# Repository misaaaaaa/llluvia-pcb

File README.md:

# llluvia-pcb

Circuito generador de gotas de lluvia lumínicas y sonoras

Fotografía por Carolina Miguieles en la inauguración de la muestra

## Descripción

El circuito utiliza un transistor NPN de manera que genera un ruido rosa. Con la base conectada a negativo, el emisor a positivo y el colector desconectado, se genera una conducción inversa a través de la unión base-emisor. Esta configuración crea fluctuaciones aleatorias de corriente que producen variaciones similares al ruido rosa, lo que asemeja el sonido de una lluvia torrencial. Esta señal es llevada a un comparador simple, al que por medio de un potenciómetro se puede controlar cuantas "gotas" se dejan pasar.

## Especificaciones

- Alimentación sugerida de 12 a 15v DC centro positivo
- Alimentación vía batería 23A o fuente de poder DC
- Potenciómetro de control de "gotas"
- Potenciómetro de control de nivel
- Salida para auriculares o de línea (revisar bugs)

## Contexto

La pcb fue diseñada para la exposición "Llluvia Metropolitana", exhibida en enero de 2026 en la Galería Metropolitana junto a Rainer Krause. Se produjeron tres modelos, todos con la misma electrónica, pero con una cita, traducción o paráfrasis distinta en cada una:

"[...] ya va a llover, ya va a llover, ya va a llover, ya va a llover, [...]" - Steve Reich

"pensar en el evento pluvial del carniense: 
la lluvia de 2 millones de años hace 234 millones de años (*archifósil*)" - Quentin Meillassoux

"¿la lluvia pertenece al mundo material, o solo los charcos que deja en zanjas y baches?" - Tim Ingold

## Bugs conocidos

- Para trabajar conectado a una fuente DC se sugiere retirar la batería de 12V 23A, ya que según el circuito solo se desconecta si ambas entradas JACK DC tienen algo conectado
- La salida L y R del conector de audio están puenteadas, por lo que si se conecta un plug MONO (TS) como los del formato Eurorack la salida se aterriza y no suena. Se sugiere intervenir la placa y romper la pista que conecta ambas salidas si se va a utilizar de esta manera. Si se usa con audífonos o con un cable TRS no hay inconvenientes.

## Bom

[Lista de materiales en formato CSV](./llluvia-bom.csv)

| Reference       | Cantidad | Value                     | Footprint                                              | Comentario                                        | Link de referencia                                                                        |
|-----------------|----------|---------------------------|--------------------------------------------------------|---------------------------------------------------|-------------------------------------------------------------------------------------------|
| C1,C2           |        2 | 1u                        | Condensador no polarizado 5.1mm x 3.2mm - Pitch 5.00mm |                                                   | ~                                                                                         |
| D1,D3,D4        |        3 | LED                       | Led 3mm cabeza plana                                   | Montaje invertido (por parte trasera de la placa) | <https://www.railwayscenics.com/flat-warm-white-water-clear-resistor-reqd-p-4583.html>      |
| D2              |        1 | 1N4007                    | Diodo THT TO-41                                        |                                                   | <http://www.vishay.com/docs/88503/1n4001.pdf>                                               |
| J2,J3           |        2 | JACK_DC                   | Conector Barrel Jack 2.1mm x 5.5 mm                    |                                                   | <https://es.rs-online.com/web/p/conectores-de-alimentacion-dc/2858785>                      |
| J4              |        1 | ON/OFF                    | Pin header 2p 2.54mm                                   |                                                   | <https://no.rs-online.com/web/p/pcb-headers/2518086>                                        |
| J5              |        1 | AudioJack2_Ground_Switch  | Jack audio TRS 3.5mm modelo CUI SJ1-3525N              |                                                   | <https://forum.digikey.com/t/cui-sj1-3525n-series-3-5mm-audio-jack-suffix-information/6667> |
| Q2              |        1 | 2N2222A                   | Transistor 2n2222a THT                                 |                                                   | <https://www.victronics.cl/transistores/transistor-pn2222a-npn-06a-40v-to92-10u/>                                        |
| R1              |        1 | 1M                        | Resistencia 1/4w                                       |                                                   | ~                                                                                         |
| R2              |        1 | 470k                      | Resistencia 1/4w                                       |                                                   | ~                                                                                         |
| R3              |        1 |                       220 | Resistencia 1/4w                                       |                                                   | ~                                                                                         |
| R4,R6,R7,R8,R11 |        5 | 1k                        | Resistencia SMD 0805                                   | Para practicar soldadura SMD a mano :D            | ~                                                                                         |
| R5,R9,R10       |        3 | 100k                      | Resistencia SMD 0805                                   | Para practicar soldadura SMD a mano :D            | ~                                                                                         |
| RV1,RV2         |        2 | 100k                      | Potenciómetro PCB tipo RV09 o PTV09A Vertical          |                                                   | <https://es.rs-online.com/web/p/potenciometros/7377827>                                     |
| U1              |        1 | LM324                     | Circuito Integrado DIP-14 + Socket                     |                                                   | <http://www.ti.com/lit/ds/symlink/lm2902-n.pdf>                                             |
| BT1             |        1 | Batería 12V A23 + Soporte | 12v A23 battery holder THT                             | Solo si se quiere usar con batería                | <https://www.jsumo.com/battery-holder-1-x-23a-with-pins>                                    |

## Esquemático

## Imágenes

## Video de referencia (01:40)

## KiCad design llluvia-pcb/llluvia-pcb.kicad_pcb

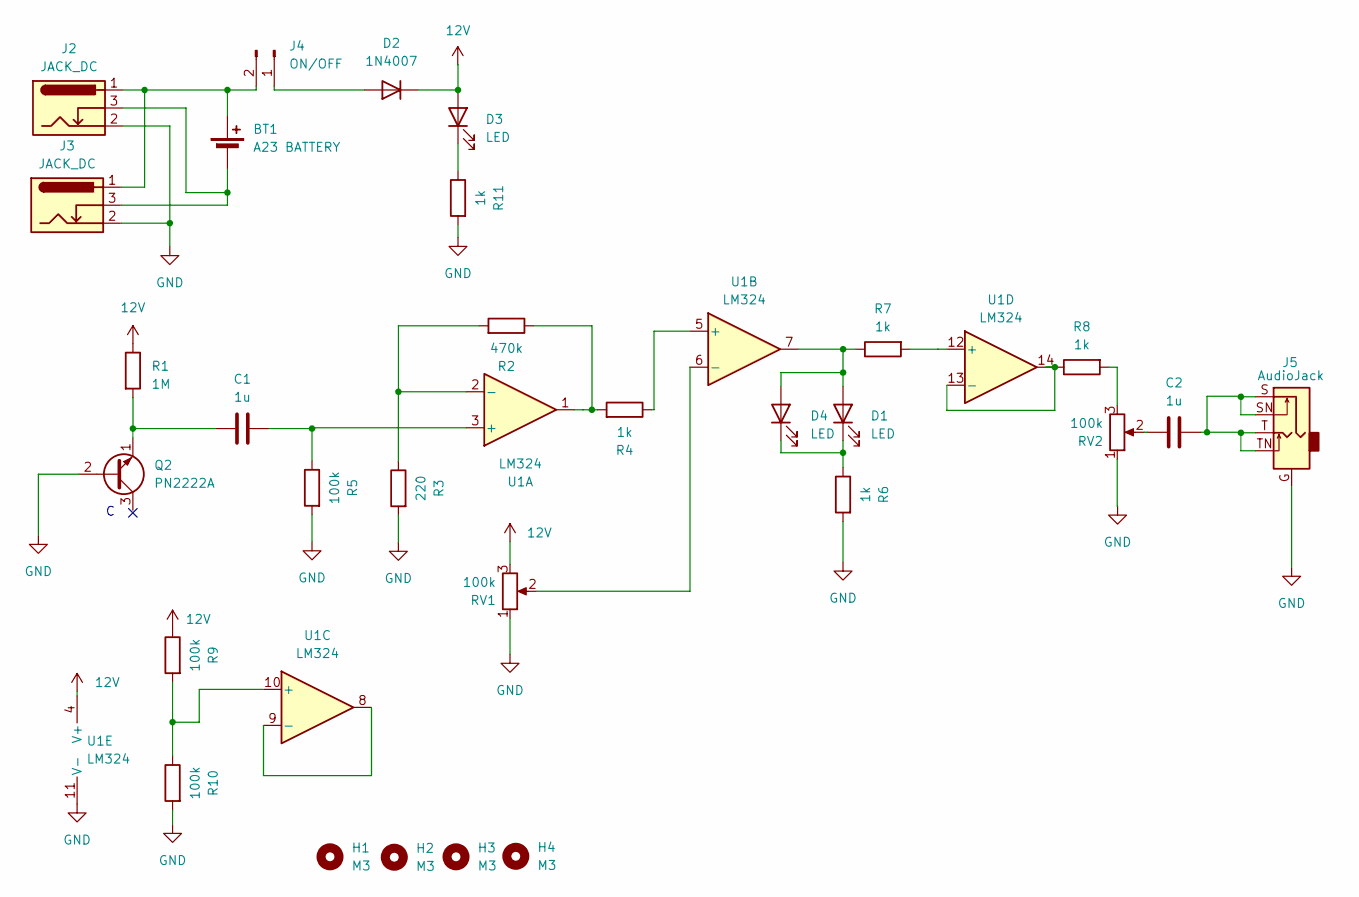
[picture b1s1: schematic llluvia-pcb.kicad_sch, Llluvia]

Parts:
BT1: A23 BATTERY; Battery_23A
C1, C2: 1u; C_Disc_D5.1mm_W3.2mm_P5.00mm
D1, D3: LED; LED_PCBasDiffuser
D2: 1N4007; D_DO-41_SOD81_P10.16mm_Horizontal
D4: LED; LED_D5.0mm
H1, H2, H3, H4: M3; MountingHole_3.2mm_M3
J2, J3: JACK_DC; BarrelJack_Horizontal
J4: ON/OFF; PinHeader_1x02_P2.54mm_Vertical
J5: AudioJack; Jack_3.5mm_CUI_SJ1-3525N_Horizontal
Q2: PN2222A; TO-92_Inline_Wide
R1: 1M; R_Axial_DIN0207_L6.3mm_D2.5mm_P10.16mm_Horizontal
R2: 470k; R_Axial_DIN0207_L6.3mm_D2.5mm_P10.16mm_Horizontal
R3: 220; R_Axial_DIN0207_L6.3mm_D2.5mm_P10.16mm_Horizontal
R4, R6, R7, R8, R11: 1k; R_0805_2012Metric_Pad1.20x1.40mm_HandSolder
R5, R9, R10: 100k; R_0805_2012Metric_Pad1.20x1.40mm_HandSolder
RV1, RV2: 100k; Potentiometer_Bourns_PTV09A-1_Single_Vertical
U1: LM324; DIP-14_W7.62mm_LongPads

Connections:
12V: D2.1 (K), D3.2 (A), R1.1, R9.1, RV1.3, U1.4 (V+)
GND: J2.2, J3.2, J5.G, Q2.2 (B), R3.2, R5.2, R6.2, R10.2, R11.2, RV1.1, RV2.1, U1.11 (V-)
unnamed: BT1.1 (+), J2.1, J3.1, J4.2
unnamed: BT1.2 (-), J2.3, J3.3
unnamed: C2.1, RV2.2
unnamed: C2.2, J5.S, J5.SN, J5.T, J5.TN
unnamed: D1.2 (A), D4.2 (A), R7.1, U1.7
unnamed: D1.1 (K), D4.1 (K), R6.1
unnamed: D2.2 (A), J4.1
unnamed: D3.1 (K), R11.1
unnamed: C1.1, Q2.1 (E), R1.2
unnamed: R2.1, R4.2, U1.1
unnamed: R8.2, RV2.3
unnamed: C1.2, R5.1, U1.3 (+)
unnamed: R2.2, R3.1, U1.2 (-)
unnamed: R4.1, U1.5 (+)
unnamed: RV1.2, U1.6 (-)
unnamed: R9.2, R10.1, U1.10 (+)
unnamed: U1.8, U1.9 (-)
unnamed: R7.2, U1.12 (+)
unnamed: R8.1, U1.13 (-), U1.14

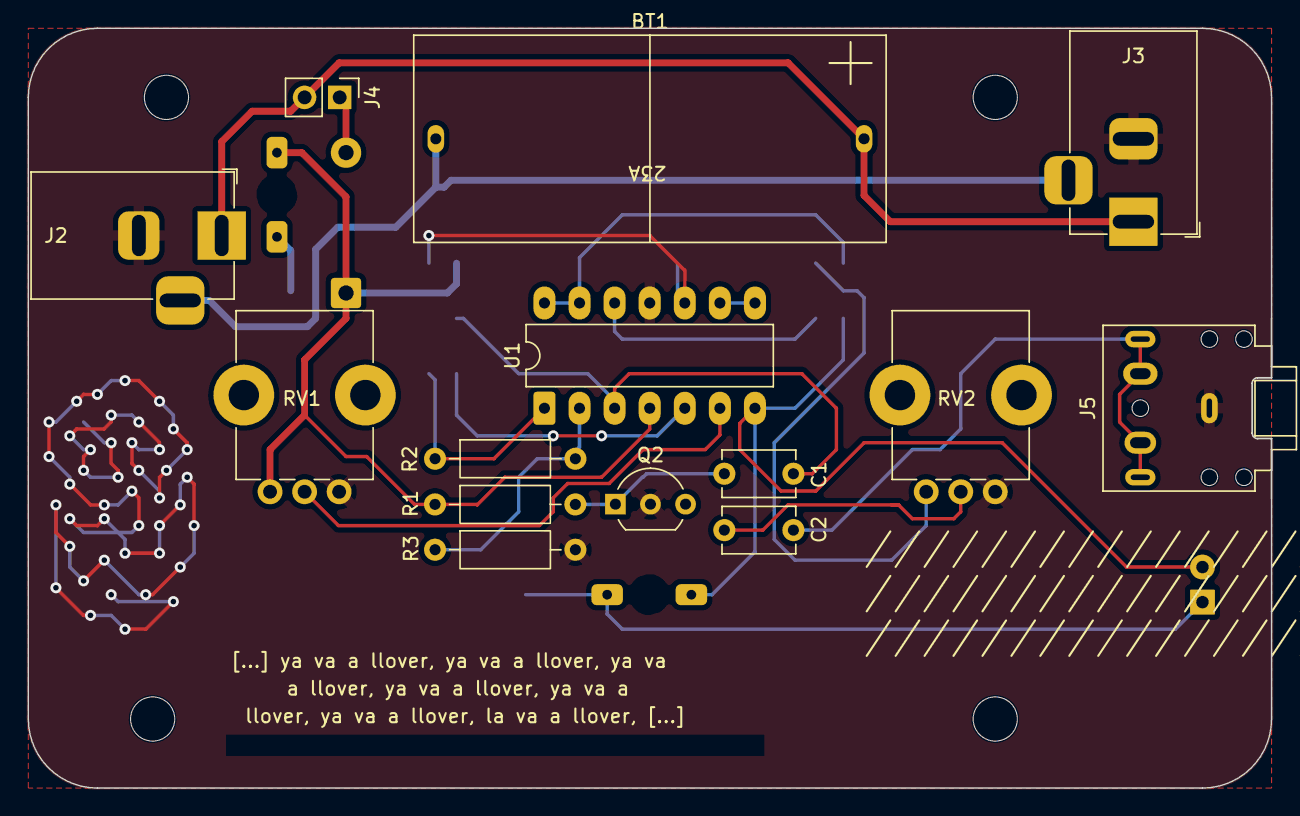
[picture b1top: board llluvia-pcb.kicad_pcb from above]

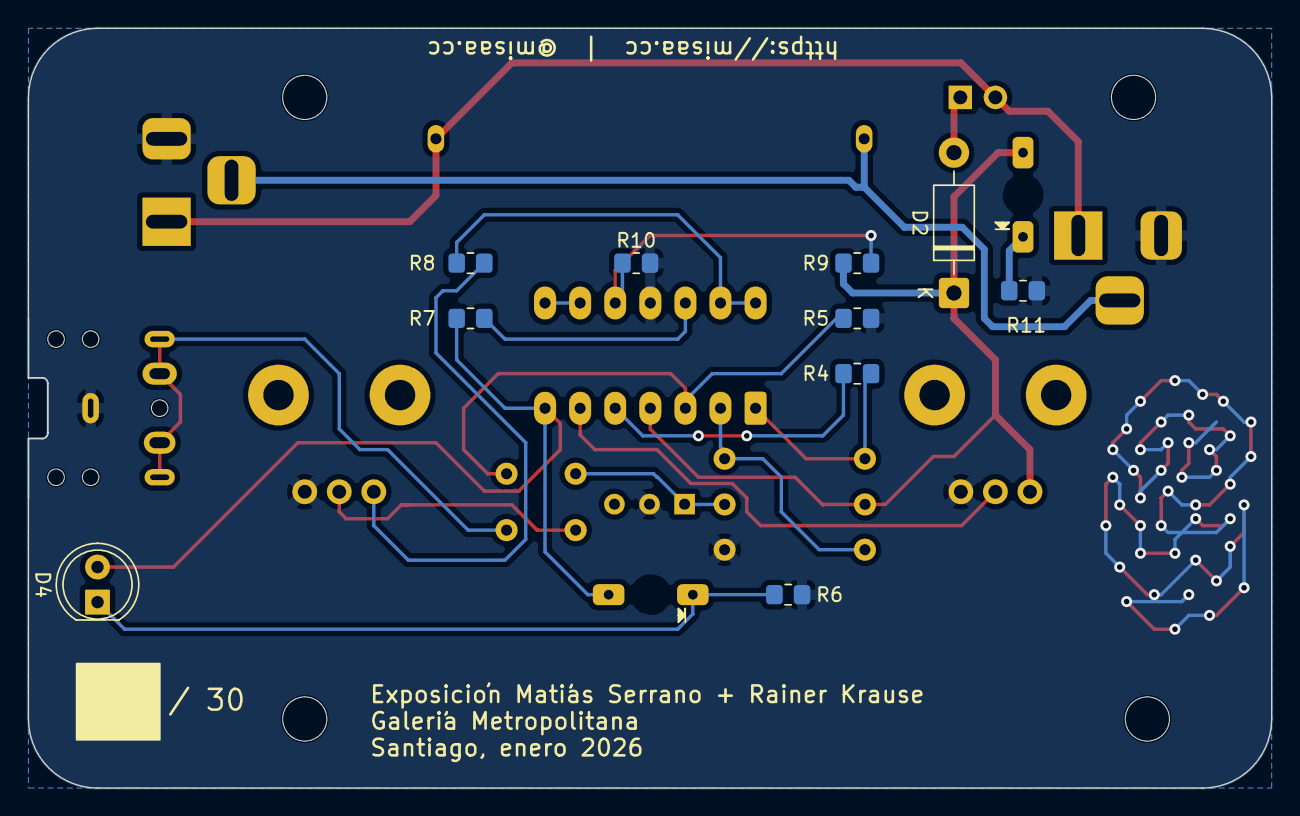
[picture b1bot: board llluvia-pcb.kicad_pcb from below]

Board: 2 copper layers, 90.0 x 55.0 mm, 30 parts (10 on the bottom side), 21 nets.

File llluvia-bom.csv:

Reference,Cantidad,Value,Footprint,Comentario,Link de referencia
"C1,C2",2,1u,Condensador no polarizado 5.1mm x 3.2mm - Pitch 5.00mm,,~
"D1,D3,D4",3,LED,Led 3mm cabeza plana,Montaje invertido (por parte trasera de la placa),https://www.railwayscenics.com/flat-warm-white-water-clear-r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
D2,1,1N4007,Diodo THT TO-41,,http://www.vishay.com/docs/88503/1n4001.pdf
"J2,J3",2,JACK_DC,Conector Barrel Jack 2.1mm x 5.5 mm,,https://es.rs-online.com/web/p/conectores-de-alimentacion-dc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
J4,1,ON/OFF,Pin header 2p 2.54mm,,https://no.rs-online.com/web/p/pcb-headers/2518086
J5,1,AudioJack2_Ground_Switch,Jack audio TRS 3.5mm modelo CUI SJ1-3525N,,https://forum.digikey.com/t/cui-sj1-3525n-series-3-5mm-audio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
Q2,1,2N2222A,Transistor 2n2222a THT ,,https://www.onsemi.com/pub/Collateral/PN2222-D.PDF
R1,1,1M,Resistencia 1/4w,,~
R2,1,470k,Resistencia 1/4w,,~
R3,1,220,Resistencia 1/4w,,~
"R4,R6,R7,R8,R11",5,1k,Resistencia SMD 0805,Para practicar soldadura SMD a mano :D,~
"R5,R9,R10",3,100k,Resistencia SMD 0805,Para practicar soldadura SMD a mano :D,~
"RV1,RV2",2,100k,Potenciómetro PCB tipo RV09 o PTV09A Vertical,,https://es.rs-online.com/web/p/potenciometros/7377827
U1,1,LM324,Circuito Integrado DIP-14 + Socket,,http://www.ti.com/lit/ds/symlink/lm2902-n.pdf
BT1,1,Batería 12V A23 + Soporte,12v A23 battery holder THT,Solo si se quiere usar con batería,https://www.jsumo.com/battery-holder-1-x-23a-with-pins

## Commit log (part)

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2026-01-28 Add .DS_Store to .gitignore
2026-02-24 añadida información circuito
2026-02-24 reducido tamaño imagen
2026-02-24 añadida cita fotografía
2026-02-27 corregido enlace 2n2222a
